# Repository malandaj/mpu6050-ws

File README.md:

# mpu6050-ws
ESP8266 Sketch to read data from a mpu6050 accelerometer/gyroscope and send it to a node.js server using web sockets.

To create standalone executable install pkg using `npm install -g pkg` and run on terminal `pkg .`

Self-signed certficate was created using OpenSSL
`openssl req -x509 -sha256 -nodes -days 3650 -newkey rsa:2048 -keyout server.key -out server.crt`

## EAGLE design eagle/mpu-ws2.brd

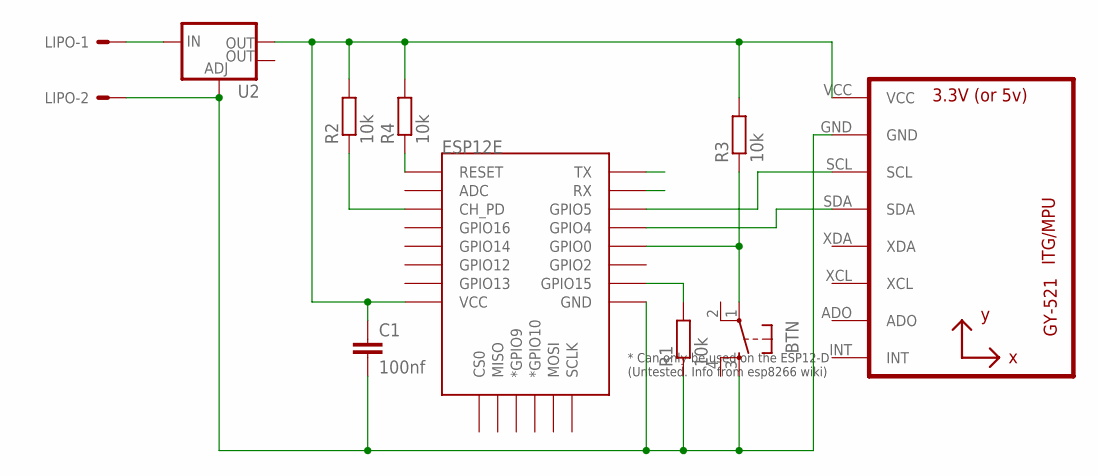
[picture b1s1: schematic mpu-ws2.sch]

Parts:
BTN: TAC_SWITCHPTH; TACTILE-PTH
C1: 100nf; C0805
ESP12E: ESP12ESMD; ESP12E-SMD
LIPO: 332-02
R1, R2, R3, R4: 10k; R0805
U2: V_REG_LM1117SOT223; SOT223
U3: GY-521MPU6050; GY-521

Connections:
5V: LIPO.1, U2.3 (IN)
CH_PD: ESP12E.CH_PD, R2.1
GND: BTN.3, C1.2, ESP12E.GND, LIPO.2, R1.1, U2.1 (ADJ), U3.GND
GPIO0: BTN.1, ESP12E.GPIO0, R3.1
GPIO4: ESP12E.GPIO4, U3.SDA
GPIO5: ESP12E.GPIO5, U3.SCL
GPIO15: ESP12E.GPIO15, R1.2
RESET: ESP12E.RESET, R4.1
RX: ESP12E.RXD0 (RX)
TX: ESP12E.TXD0 (TX)
VCC: C1.1, ESP12E.VCC, R2.2, R3.2, R4.2, U2.2 (OUT), U3.VCC

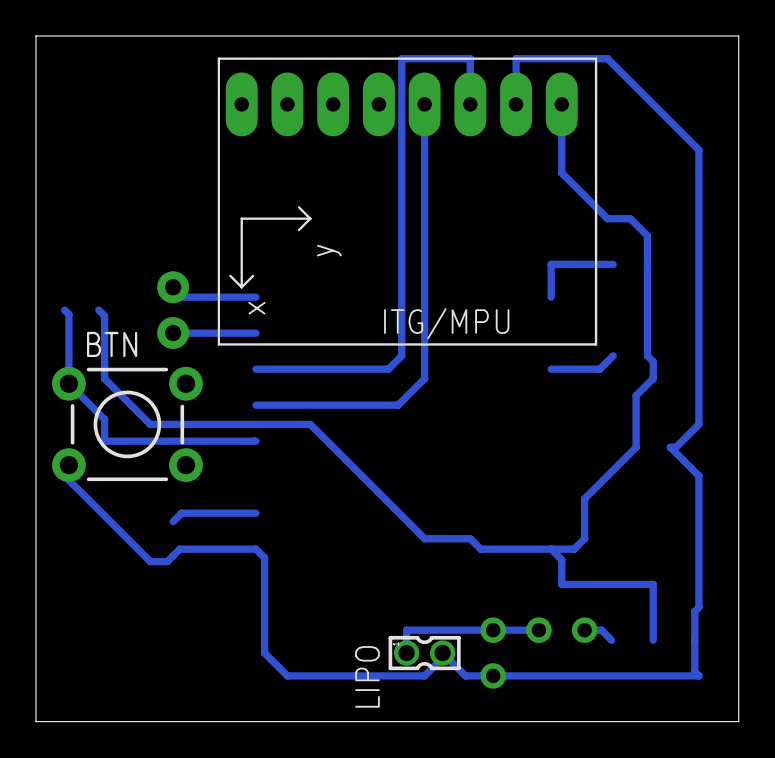
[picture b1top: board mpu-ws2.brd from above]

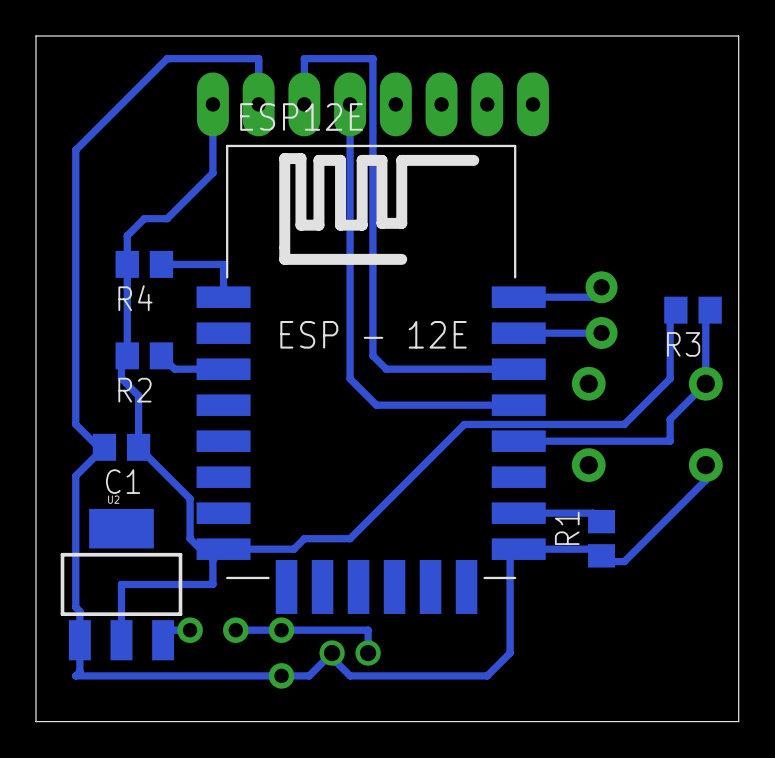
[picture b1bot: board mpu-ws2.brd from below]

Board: 2 copper layers, 39.0 x 38.1 mm, 10 parts (7 on the bottom side), 9 nets.

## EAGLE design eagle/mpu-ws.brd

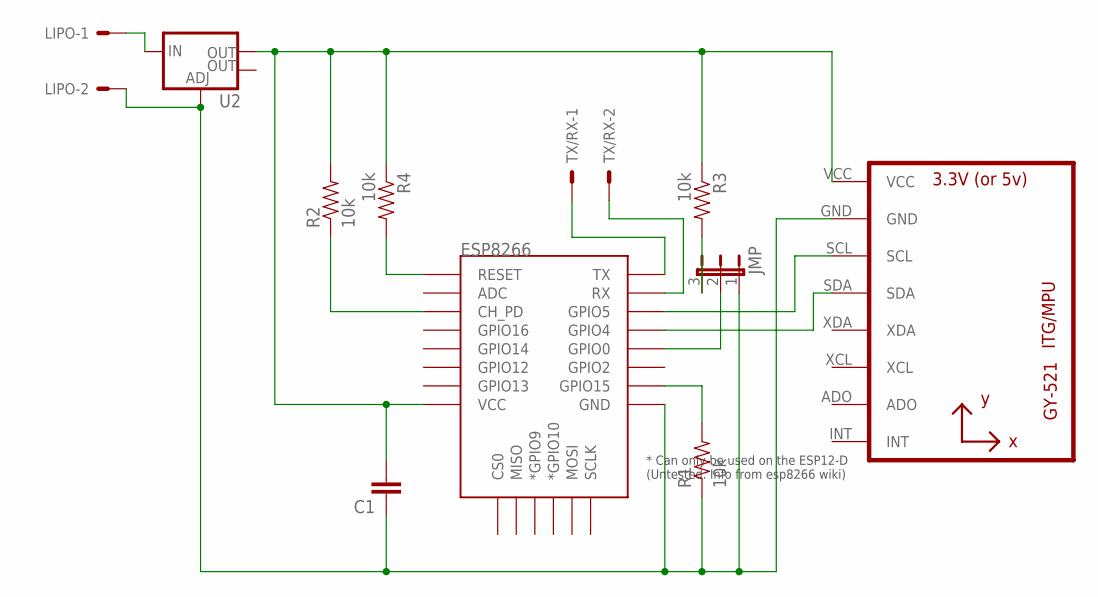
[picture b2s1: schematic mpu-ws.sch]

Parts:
C1: C-EU025-024X044; C025-024X044
ESP8266: ESP12ESMD; ESP12E-SMD
JMP: JP2E; JP2
LIPO: 332-02
R1, R2, R3: 10k; AXIAL-0.1EZ
R4: 10k; AXIAL-0.1
TX/RX: 332-02
U1: GY-521MPU6050; GY-521
U2: V_REG_LM1117SOT223; SOT223

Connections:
5V: LIPO.1, U2.3 (IN)
CH_PD: ESP8266.CH_PD, R2.P$1 (1)
GND: C1.1, ESP8266.GND, JMP.1, LIPO.2, R1.P$1 (1), U1.GND, U2.1 (ADJ)
GPIO0: ESP8266.GPIO0, JMP.2
GPIO15: ESP8266.GPIO15, R1.P$2 (2)
PULLUP: JMP.3, R3.P$2 (2)
RESET: ESP8266.RESET, R4.P$2 (2)
RX: ESP8266.RXD0 (RX), TX/RX.2
SCL: ESP8266.GPIO5, U1.SCL
SDA: ESP8266.GPIO4, U1.SDA
TX: ESP8266.TXD0 (TX), TX/RX.1
VCC: C1.2, ESP8266.VCC, R2.P$2 (2), R3.P$1 (1), R4.P$1 (1), U1.VCC, U2.2 (OUT)

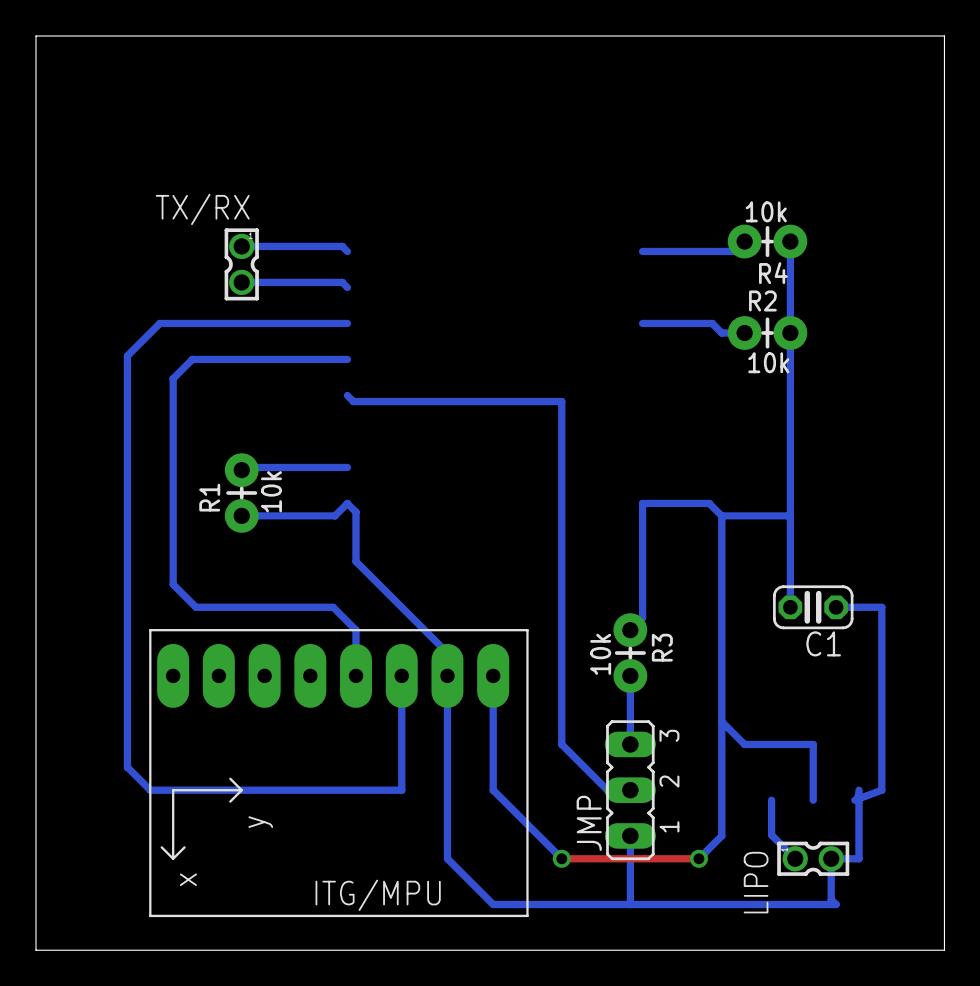
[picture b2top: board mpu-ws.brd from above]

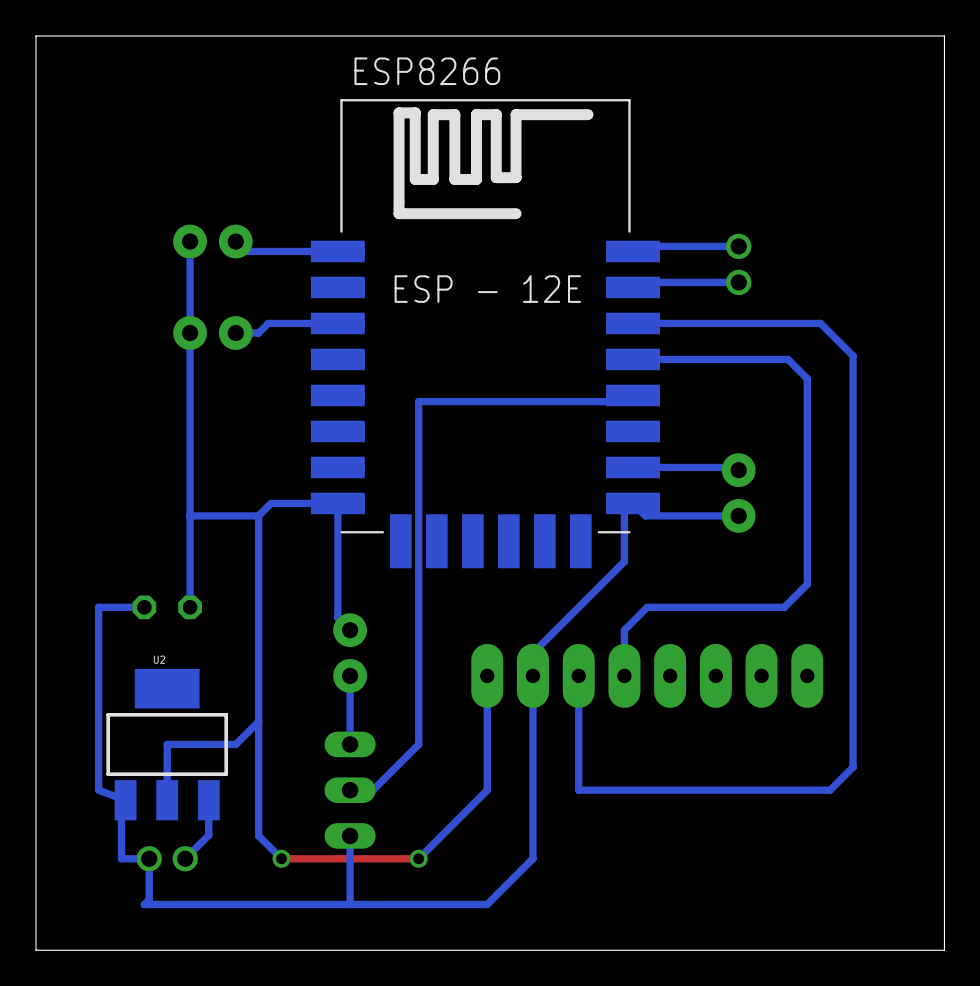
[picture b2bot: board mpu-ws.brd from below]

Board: 2 copper layers, 50.5 x 50.8 mm, 11 parts (2 on the bottom side), 12 nets.

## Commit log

2016-05-20 initial
2016-05-29 ssid and pass
2016-05-30 addded expressjs
2016-05-30 add gitignore
2016-05-30 add express
2016-05-30 somthing
2016-05-30 added index page
2016-05-30 change name
2016-05-30 added fonts and changed index
2016-05-30 added canvasjs
2016-05-30 added dependencies
2016-05-30 send message to all connected clients
2016-05-30 addded charts
2016-05-31 fluid layout
2016-05-31 startPreview button
2016-06-07 add lowdb to save data to json
2016-06-07 database example
2016-06-12 ws error handling
2016-06-13 download data as json file
2016-06-13 offline plotting with python
2016-06-19 addded WiFi manager library
2016-06-24 change acc and gyro sensitivity
2016-06-24 change default wire pins
2016-09-07 properly close SPIFFS after usage. change wire pins to default.
2016-09-08 wifi config
2016-09-08 add mpu6050 support
2016-09-09 agregado websocket
2016-09-11 change subprotocol name for clients
2016-09-11 remove wifi manager library
2016-09-12 change serialize method, added buffer to send data
2016-09-12 change folder structure
2016-09-13 code refactoring, parsing json buffer, ...
2016-09-14 change package size
2016-09-27 Added calibration parameters, minor changes
2016-10-03 added calibration control from web ui
2016-10-04 added lowdb to save data to json file
2016-10-05 added export to csv functionality
2016-10-07 added export to csv function
2016-10-07 minor changes
2016-10-07 added plot from csv file
2016-10-07 more than one sensor data in same plot
2016-10-08 change labels for axes
2016-10-18 add csv data
2016-10-23 change variable type
2016-11-07 remove python stuff
2017-02-07 add eagle schematic and board
2017-02-09 change pcb board
2017-02-10 pcb board
2017-02-23 nuevo diseño
2017-05-05 save data as zip file
2017-05-05 format filename of data
2017-05-10 add ota updates
2017-05-16 add callback to fs.writeFile to avoid deprecation warning
2017-05-27 catch parse exception
2017-06-02 static calibration offsets and an sketch to calculate them
2017-06-02 use smoothie.js to plot real time data
2017-06-08 fix error that was causing an empty data file
2017-06-08 comment lines that crash with node 8
2017-06-08 downgrade lowdb to v.13.1
2017-09-11 catch ws errors, remove calibration variables from esp8266 program
2017-09-25 add seconds to filename
2017-10-10 add notifications on connect/disconnect cell phone
2017-10-11 open browser automatically
2017-12-01 change background color
2017-12-01 remove unused prints
2017-12-01 change line width
2017-12-01 change gridline color
2018-08-31 upgrade libraries
2018-09-19 agregado sonido cuando se desconecta
2018-09-21 add server to check calibration
2018-09-21 modify readme.md
2018-09-26 change async file write to sync
2018-09-26 add async db write
2018-11-14 using SSL and WSS with self signed certificate
2018-11-20 change certificate expiration date

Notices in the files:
parts and their libraries:
SparkFun-Resistors: Licensing: Creative Commons ShareAlike 4.0 International - https://creativecommons.org/licenses/by-sa/4.0
